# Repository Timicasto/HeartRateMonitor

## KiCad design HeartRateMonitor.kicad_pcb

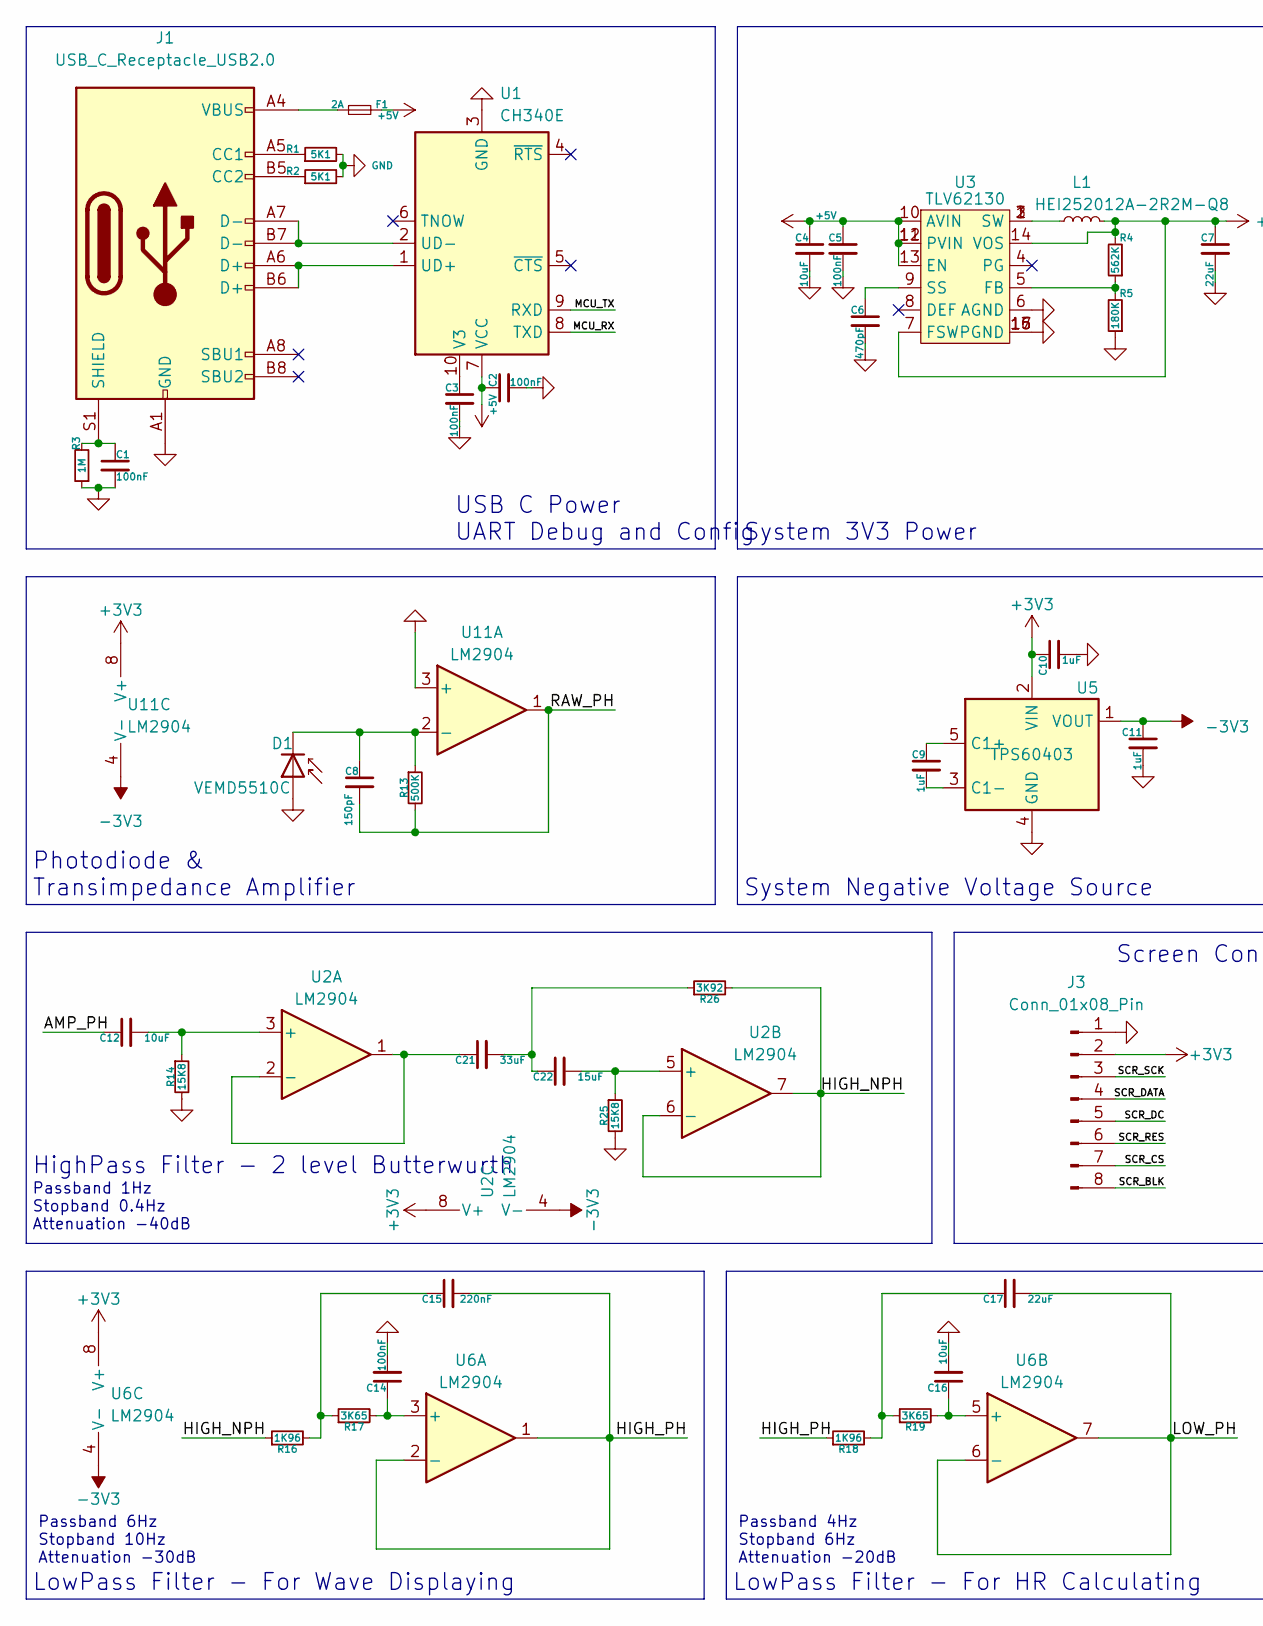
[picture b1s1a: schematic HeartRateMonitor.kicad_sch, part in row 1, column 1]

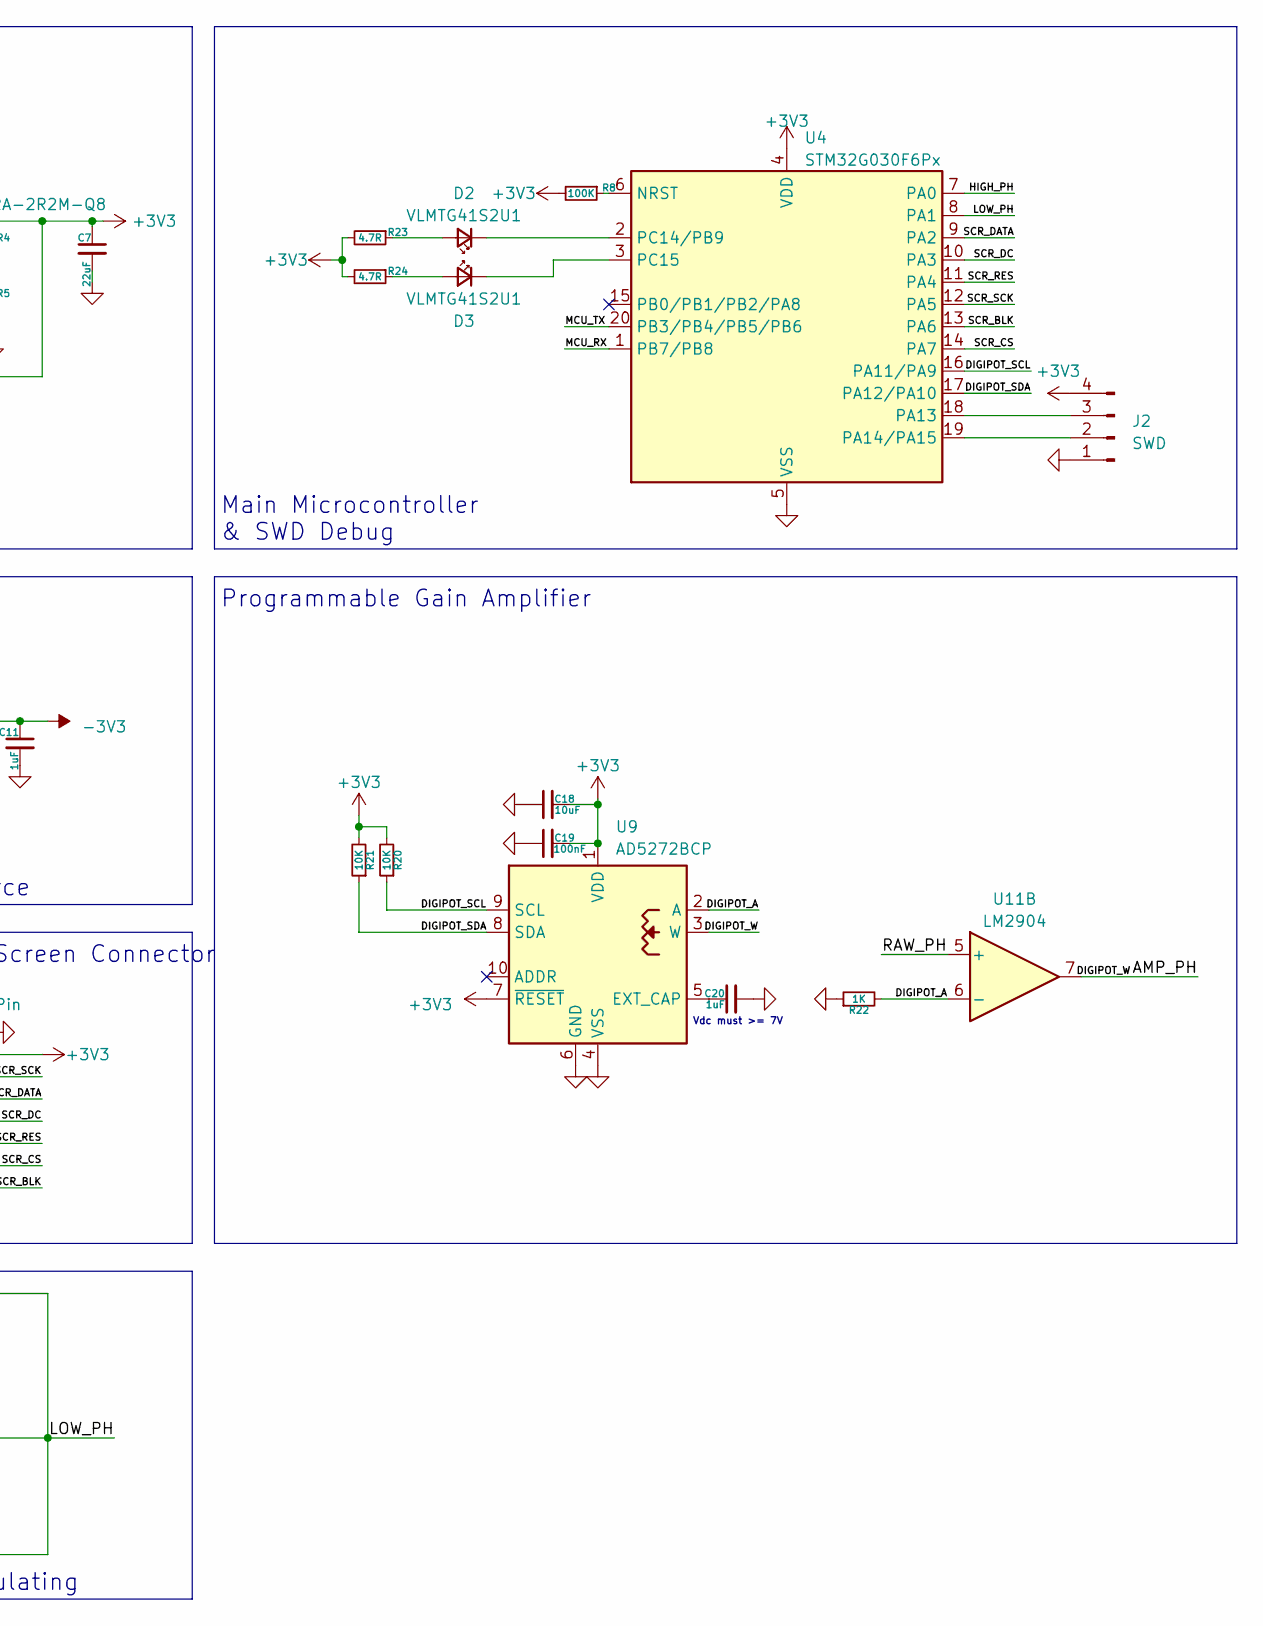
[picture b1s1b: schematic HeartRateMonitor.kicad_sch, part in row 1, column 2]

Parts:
C1, C2, C3, C5, C14, C19: 100nF; C_0603_1608Metric
C4, C12, C16, C18: 10uF; C_0603_1608Metric
C6: 470pF; C_0603_1608Metric
C7, C17: 22uF; C_0603_1608Metric
C8: 150pF; C_0603_1608Metric
C9, C10, C11, C20: 1uF; C_0603_1608Metric
C15: 220nF; C_0603_1608Metric
C21: 33uF; C_1206_3216Metric
C22: 15uF; C_0402_1005Metric
D1: VEMD5510C
D2, D3: VLMTG41S2U1; CP_EIA-3528-21_Kemet-B
F1: 2A; Fuse_0805_2012Metric
J1: USB_C_Receptacle_USB2.0; TYPE-C-SMD_HX-TYPE-C-16PIN
J2: SWD; PinHeader_1x04_P2.54mm_Vertical
J3: Conn_01x08_Pin; PinHeader_1x08_P2.54mm_Vertical
L1: HEI252012A-2R2M-Q8; L_1008_2520Metric
R1, R2: 5K1; R_0603_1608Metric
R3: 1M; R_0603_1608Metric
R4: 562K; R_0603_1608Metric
R5: 180K; R_0603_1608Metric
R8: 100K; R_0603_1608Metric
R13: 500K; R_0603_1608Metric
R14, R25: 15K8; R_0603_1608Metric
R16, R18: 1K96; R_0603_1608Metric
R17, R19: 3K65; R_0603_1608Metric
R20, R21: 10K; R_0603_1608Metric
R22: 1K; R_0603_1608Metric
R23, R24: 4.7R; R_0603_1608Metric
R26: 3K92; R_0603_1608Metric
U1: CH340E; MSOP-10_3x3mm_P0.5mm
U2, U6, U11: LM2904; VSSOP-8_3.0x3.0mm_P0.65mm
U3: TLV62130; VQFN-16-1EP_3x3mm_P0.5mm_EP1.68x1.68mm
U4: STM32G030F6Px; TSSOP-20_4.4x6.5mm_P0.65mm
U5: TPS60403; SOT-23-5
U9: AD5272BCP; LFCSP-WD-10-1EP_3x3mm_P0.5mm_EP1.64x2.38mm

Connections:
+3V3: C7.1, C10.1, C18.2, C19.2, J2.4, J3.2, L1.2, R4.2, R8.2, R20.2, R21.2, R23.2, R24.2, U2.8 (V+), U3.7 (FSW), U3.14 (VOS), U4.4 (VDD), U5.2 (VIN), U6.8 (V+), U9.1 (VDD), U9.7 (~RESET), U11.8 (V+)
+5V: C2.1, C4.1, C5.1, F1.2, U1.7 (VCC), U3.10 (AVIN), U3.11 (PVIN), U3.12 (PVIN), U3.13 (EN)
-3V3: C11.1, U2.4 (V-), U5.1 (VOUT), U6.4 (V-), U11.4 (V-)
/AMP_PH: C12.1, U9.3 (W), U11.7
/DIGIPOT_A: R22.2, U9.2 (A), U11.6 (-)
/DIGIPOT_SCL: R20.1, U4.16 (PA11/PA9), U9.9 (SCL)
/DIGIPOT_SDA: R21.1, U4.17 (PA12/PA10), U9.8 (SDA)
/HIGH_PH: C15.2, R18.1, U4.7 (PA0), U6.1, U6.2 (-)
/LOW_PH: C17.2, U4.8 (PA1), U6.6 (-), U6.7
/MCU_RX: U1.8 (TXD), U4.1 (PB7/PB8)
/MCU_TX: U1.9 (RXD), U4.20 (PB3/PB4/PB5/PB6)
/RAW_PH: C8.2, R13.2, U11.1, U11.5 (+)
/SCR_BLK: J3.8, U4.13 (PA6)
/SCR_CS: J3.7, U4.14 (PA7)
/SCR_DATA: J3.4, U4.9 (PA2)
/SCR_DC: J3.5, U4.10 (PA3)
/SCR_RES: J3.6, U4.11 (PA4)
/SCR_SCK: J3.3, U4.12 (PA5)
GND: C1.2, C2.2, C3.2, C4.2, C5.2, C6.2, C7.2, C10.2, C11.2, C14.2, C16.2, C18.1, C19.1, C20.2, D1.2 (A), J1.A1 (GND), J1.A12 (GND), J1.B1 (GND), J1.B12 (GND), J2.1, J3.1, R1.2, R2.2, R3.1, R5.1, R14.2, R22.1, R25.2, U1.3 (GND), U3.6 (AGND), U3.15 (PGND), U3.16 (PGND), U3.17 (PGND), U4.5 (VSS), U5.4 (GND), U9.4 (VSS), U9.6 (GND), U9.11 (VSS), U11.3 (+)
unnamed: C15.1, R16.2, R17.1
unnamed: C17.1, R18.2, R19.1
unnamed: C21.2, C22.1, R26.1
unnamed: C8.1, D1.1 (K), R13.1, U11.2 (-)
unnamed: D2.2 (A), R23.1
unnamed: D2.1 (K), U4.2 (PC14/PB9)
unnamed: D3.2 (A), R24.1
unnamed: D3.1 (K), U4.3 (PC15)
unnamed: F1.1, J1.A4 (VBUS), J1.A9 (VBUS), J1.B4 (VBUS), J1.B9 (VBUS)
unnamed: J1.A5 (CC1), R1.1
unnamed: J1.B5 (CC2), R2.1
unnamed: C1.1, J1.S1 (SHIELD), R3.2
unnamed: J2.2, U4.19 (PA14/PA15)
unnamed: J2.3, U4.18 (PA13)
unnamed: L1.1, U3.1 (SW), U3.2 (SW), U3.3 (SW)
unnamed: J1.A6 (D+), J1.B6 (D+), U1.1 (UD+)
unnamed: J1.A7 (D-), J1.B7 (D-), U1.2 (UD-)
unnamed: C3.1, U1.10 (V3)
unnamed: C12.2, R14.1, U2.3 (+)
unnamed: C21.1, U2.1, U2.2 (-)
unnamed: C22.2, R25.1, U2.5 (+)
unnamed: R16.1, R26.2, U2.6 (-), U2.7
unnamed: R4.1, R5.2, U3.5 (FB)
unnamed: C6.1, U3.9 (SS)
unnamed: R8.1, U4.6 (NRST)
unnamed: C9.1, U5.5 (C1+)
unnamed: C9.2, U5.3 (C1-)
unnamed: C14.1, R17.2, U6.3 (+)
unnamed: C16.1, R19.2, U6.5 (+)
unnamed: C20.1, U9.5 (EXT_CAP)

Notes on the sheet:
System 3V3 Power
Photodiode & Transimpedance Amplifier
HighPass Filter - 2 level Butterwurth
Passband 4Hz Stopband 6Hz Attenuation -20dB
LowPass Filter - For HR Calculating
Passband 6Hz Stopband 10Hz Attenuation -30dB
Screen Connector
USB C Power UART Debug and Config
Vdc must >= 7V
Passband 1Hz Stopband 0.4Hz Attenuation -40dB
Programmable Gain Amplifier
System Negative Voltage Source
LowPass Filter - For Wave Displaying
Main Microcontroller & SWD Debug

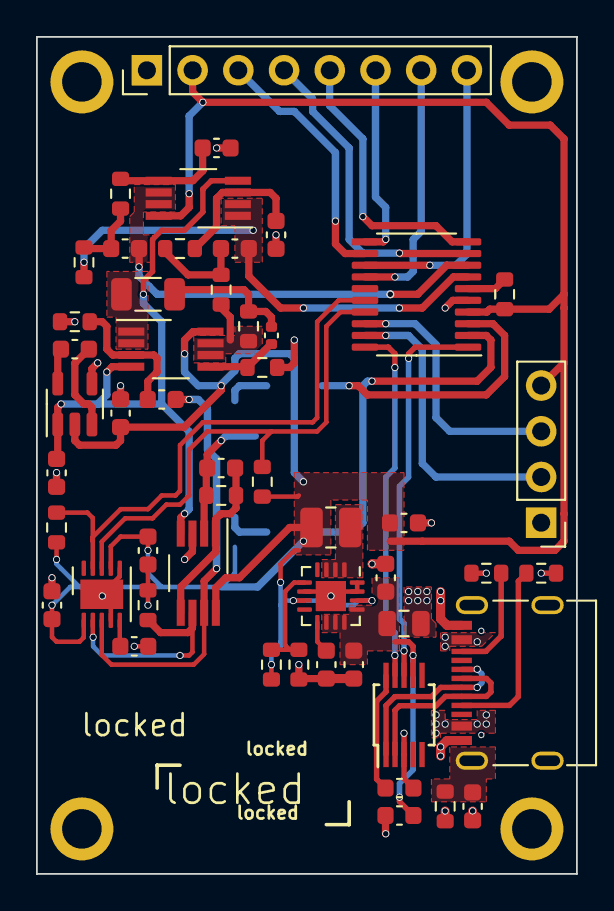
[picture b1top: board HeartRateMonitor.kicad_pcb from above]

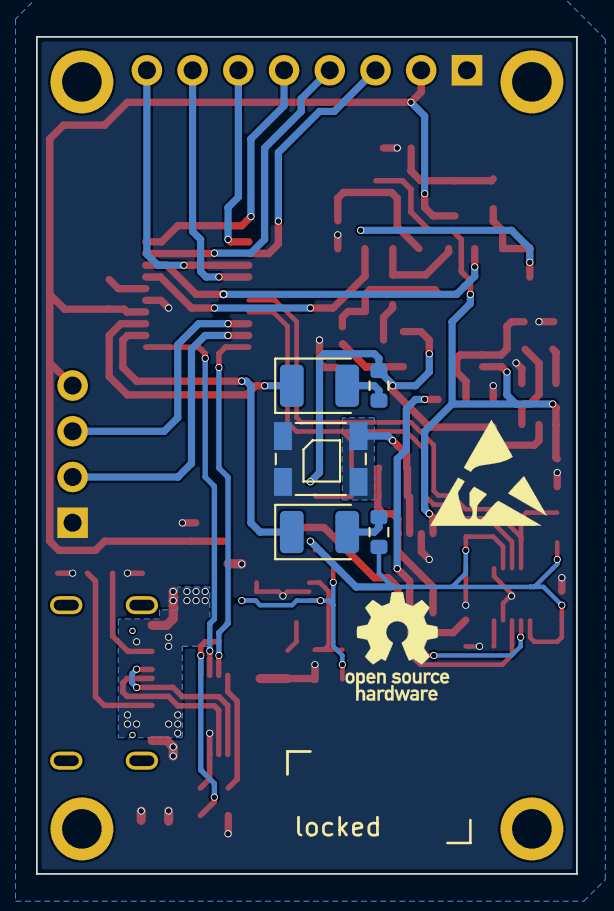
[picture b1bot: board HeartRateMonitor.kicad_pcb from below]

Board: 2 copper layers, 30.0 x 46.5 mm, 56 parts (5 on the bottom side), 49 nets.

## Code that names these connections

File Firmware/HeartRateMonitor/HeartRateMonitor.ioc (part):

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Mcu.Name=STM32G030F6Px
Mcu.Package=TSSOP20
Mcu.UserName=STM32G030F6Px
PA0.Mode=IN0
PA0.Signal=ADC1_IN0
PA1.Mode=IN1
PA1.Signal=ADC1_IN1
PA11\ [PA9].Mode=I2C
PA11\ [PA9].Signal=I2C2_SCL
PA12\ [PA10].Mode=I2C
PA12\ [PA10].Signal=I2C2_SDA
PA13.Mode=Serial_Wire
PA13.Signal=SYS_SWDIO
PA14-BOOT0.Mode=Serial_Wire
PA14-BOOT0.Signal=SYS_SWCLK
PA14-BOOT0__PA15.StandardMode=true
PA2.GPIOParameters=GPIO_Speed,PinState,GPIO_Label
PA2.GPIO_Label=SCREEN_SDA
PA2.GPIO_Speed=GPIO_SPEED_FREQ_HIGH
PA2.PinState=GPIO_PIN_RESET
PA2.Signal=GPIO_Output
PA3.GPIOParameters=GPIO_Speed,GPIO_Label
PA3.GPIO_Label=SCREEN_DC
PA3.GPIO_Speed=GPIO_SPEED_FREQ_HIGH
PA3.Signal=GPIO_Output
PA4.GPIOParameters=GPIO_Speed,GPIO_Label
PA4.GPIO_Label=SCREEN_RES
PA4.GPIO_Speed=GPIO_SPEED_FREQ_HIGH
PA4.Signal=GPIO_Output
PA5.GPIOParameters=GPIO_Speed,GPIO_Label
PA5.GPIO_Label=SCREEN_SCL
PA5.GPIO_Speed=GPIO_SPEED_FREQ_HIGH
PA5.Signal=GPIO_Output
PA6.GPIOParameters=GPIO_Speed,GPIO_Label
PA6.GPIO_Label=SCREEN_BLK
PA6.GPIO_Speed=GPIO_SPEED_FREQ_HIGH
PA6.Signal=GPIO_Output
PA7.GPIOParameters=GPIO_Speed,GPIO_Label
PA7.GPIO_Label=SCREEN_CS
PA7.GPIO_Speed=GPIO_SPEED_FREQ_HIGH
PA7.Signal=GPIO_Output
PB0__PB1__PB2__PA8.StandardMode=true
PB3__PB4__PB5__PB6.StandardMode=true
PB6.Mode=Asynchronous
PB6.Signal=USART1_TX
PB7.Mode=Asynchronous
PB7.Signal=USART1_RX
PB7__PB8.StandardMode=true
PC14-OSC32_IN\ (PC14).GPIOParameters=GPIO_Label
PC14-OSC32_IN\ (PC14).GPIO_Label=LED1
PC14-OSC32_IN\ (PC14).Signal=GPIO_Output
PC14-OSC32_IN\ (PC14)__PB9.StandardMode=true
PC15-OSC32_OUT\ (PC15).GPIOParameters=GPIO_Label
PC15-OSC32_OUT\ (PC15).GPIO_Label=LED2
PC15-OSC32_OUT\ (PC15).Signal=GPIO_Output
RCC.HSE_VALUE=8000000
RCC.SYSCLKFreq_VALUE=64000000
RCC.SYSCLKSource=RCC_SYSCLKSOURCE_PLLCLK
board=custom

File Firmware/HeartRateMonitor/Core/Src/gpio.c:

/* USER CODE BEGIN Header */
/**
  ******************************************************************************
  * @file    gpio.c
  * @brief   This file provides code for the configuration
  *          of all used GPIO pins.
  ******************************************************************************
  * @attention
  *
  * Copyright (c) 2023 STMicroelectronics.
  * All rights reserved.
  *
  * This software is licensed under terms that can be found in the LICENSE file
  * in the root directory of this software component.
  * If no LICENSE file comes with this software, it is provided AS-IS.
  *
  ******************************************************************************
  */
/* USER CODE END Header */

/* Includes ------------------------------------------------------------------*/
#include "gpio.h"

/* USER CODE BEGIN 0 */

/* USER CODE END 0 */

/*----------------------------------------------------------------------------*/
/* Configure GPIO                                                             */
/*----------------------------------------------------------------------------*/
/* USER CODE BEGIN 1 */

/* USER CODE END 1 */

/** Configure pins as
        * Analog
        * Input
        * Output
        * EVENT_OUT
        * EXTI
        * Free pins are configured automatically as Analog (this feature is enabled through
        * the Code Generation settings)
*/
void MX_GPIO_Init(void)
{

  GPIO_InitTypeDef GPIO_InitStruct = {0};

  /* GPIO Ports Clock Enable */
  __HAL_RCC_GPIOB_CLK_ENABLE();
  __HAL_RCC_GPIOC_CLK_ENABLE();
  __HAL_RCC_GPIOA_CLK_ENABLE();

  /*Configure GPIO pin Output Level */
  HAL_GPIO_WritePin(GPIOC, LED1_Pin|LED2_Pin, GPIO_PIN_RESET);

  /*Configure GPIO pin Output Level */
  HAL_GPIO_WritePin(GPIOA, SCREEN_SDA_Pin|SCREEN_DC_Pin|SCREEN_RES_Pin|SCREEN_SCL_Pin
                          |SCREEN_BLK_Pin|SCREEN_CS_Pin, GPIO_PIN_RESET);

  /*Configure GPIO pins : PB8 PB9 PB0 PB1
                           PB2 PB3 PB4 PB5 */
  GPIO_InitStruct.Pin = GPIO_PIN_8|GPIO_PIN_9|GPIO_PIN_0|GPIO_PIN_1
                          |GPIO_PIN_2|GPIO_PIN_3|GPIO_PIN_4|GPIO_PIN_5;
  GPIO_InitStruct.Mode = GPIO_MODE_ANALOG;
  GPIO_InitStruct.Pull = GPIO_NOPULL;
  HAL_GPIO_Init(GPIOB, &GPIO_InitStruct);

  /*Configure GPIO pins : PCPin PCPin */
  GPIO_InitStruct.Pin = LED1_Pin|LED2_Pin;
  GPIO_InitStruct.Mode = GPIO_MODE_OUTPUT_PP;
  GPIO_InitStruct.Pull = GPIO_NOPULL;
  GPIO_InitStruct.Speed = GPIO_SPEED_FREQ_LOW;
  HAL_GPIO_Init(GPIOC, &GPIO_InitStruct);

  /*Configure GPIO pins : PAPin PAPin PAPin PAPin
                           PAPin PAPin */
  GPIO_InitStruct.Pin = SCREEN_SDA_Pin|SCREEN_DC_Pin|SCREEN_RES_Pin|SCREEN_SCL_Pin
                          |SCREEN_BLK_Pin|SCREEN_CS_Pin;
  GPIO_InitStruct.Mode = GPIO_MODE_OUTPUT_PP;
  GPIO_InitStruct.Pull = GPIO_NOPULL;
  GPIO_InitStruct.Speed = GPIO_SPEED_FREQ_HIGH;
  HAL_GPIO_Init(GPIOA, &GPIO_InitStruct);

  /*Configure GPIO pins : PA8 PA15 */
  GPIO_InitStruct.Pin = GPIO_PIN_8|GPIO_PIN_15;
  GPIO_InitStruct.Mode = GPIO_MODE_ANALOG;
  GPIO_InitStruct.Pull = GPIO_NOPULL;
  HAL_GPIO_Init(GPIOA, &GPIO_InitStruct);

}

/* USER CODE BEGIN 2 */

/* USER CODE END 2 */

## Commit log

2023-04-14 init
2023-04-16 firmware template and PCB constrains
2023-04-19 add TIA
2023-04-19 low and high pass filter
2023-04-20 answer(((
2023-04-21 refactor
2023-04-21 flash overflow
2023-04-22 layout
2023-04-22 add .gitignore
2023-04-22 modify latout
2023-04-22 merge
2023-04-22 add LED
2023-04-23 slight modify layout
2023-04-24 success 1/2 (?)
2023-04-24 0.9 (?)
2023-04-24 completed, left DRC unchecked
2023-04-24 reconstruct
2023-04-27 heart rate calculate
2023-04-27 ADC DMA Timer
2023-04-27 data validation and sync
2023-04-28 slightly modified filter and generated fabrication output
2023-05-04 finalize hardware
2023-05-14 LCD Device Driver and Migrated to Makefile
2023-05-14 Makefile
2023-05-14 font rendering
2023-05-16 update main (test)
2023-05-17 Changed SPI configuration (8MBit/s LSB First)
2023-05-17 test update
2023-05-17 Change BKLT to Open Drain Output
2023-05-19 rm build
2023-05-19 fix drawfont
2023-05-19 ADC conversion IT via UART
2023-05-19 open led
2023-05-19 Added TIM IRQ
2023-05-20 add print lib
2023-05-20 add shell
2023-05-20 complete print
2023-05-20 slight modify
2023-05-22 Fix: AD5272 I2C Timing
2023-05-23 Add PGA lib
2023-05-24 modify spi rate
2023-05-24 try to fix screen,failed
2023-05-24 fix PGA
2023-05-24 Add PGA to makefile
2023-05-24 Use PGA in main
2023-05-24 Feat: Migrated Beat rate algorithm into ADC IT
2023-05-24 modify time scale
2023-05-25 fix print
2023-05-25 update beat
2023-05-25 changed timer config method
2023-05-25 fix timer
2023-05-25 try to fix beat
2023-05-25 fix beat x2
2023-05-25 rewrite algorithm
2023-05-25 modify main Init
2023-05-25 add getRate, ready to test
2023-05-26 fix beat
2023-05-26 changed to software emulated SPI
2023-05-26 fix area size calculation
2023-05-26 Fix init in main
2023-05-30 add TeX
2023-05-30 Report: 4 - Hardware
2023-05-30 Report: 5 - Software
2023-05-30 Report: 6 - Power test
2023-05-31 Report:8 - Test report, Conclusion and Legal disclaimer
2023-05-31 Report:8 - Fix typo
2023-05-31 Report:7 - Conclusion generated by AI
2023-05-31 Add legal information
2023-05-31 Code cleanup
2023-05-31 Hardware Cleanup
2023-05-31 Fix PCB Layout PDF
2023-05-31 Report - Appendix
2023-06-01 fix '~'
2023-06-01 modify thanks
2023-06-01 add software design figure
2023-06-01 add signature
2023-06-01 Fix margin
2023-06-01 Fix paper overflow

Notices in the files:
HeartRateMonitor.kicad_pcb:
SPDX License: CERN-OHL-P-2.0
